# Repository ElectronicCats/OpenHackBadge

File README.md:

# Badge OpenHack Guatemala

Este es un badge electronico que hemos creado para nuestros amigos de OpenHack Guatemala 2019, en este repositorio encontraras todos los archivos necesarios para conocer el badge, ahora saca el maximo pontencial de tu badge.

### Installation Instructions

**Install SAMD soport**

You must install the boards SAMD of Arduino(vertions 1.6.11 o posterior) 

In the menú bar selec tools --> boards --> Board Manager --> Arduino SAMD Boards 32 bit M0.

In the search bar write  "SAMD" en then you can see the boards, do clic in install and wait to finish to installe.

To add board support for our products, start Arduino and open the Preferences window (**File** > **Preferences**). Now copy and paste the following URL into the 'Additional Boards Manager URLs' input field:

	https://electroniccats.github.io/Arduino_Boards_Index/package_electroniccats_index.json

- If there is already an URL from another manufacturer in that field, click the button at the right end of the field. This will open an editing window allowing you to paste the above URL onto a new line.

- Press the "OK" button.
- Open the "boards manager" that is in tools --> Board --> board manager.
- Now write "Electronic Cats" (without quotes) in the search bar.
- Click in install, jus wait to finish to install and only close the window. 

- In tools --> Boards, scroll to down in the board´s list you can see the Electronic Cat´s boards.

8. Close Boards Manager, then click Tools->Board->samd11 generic.
9. Select the MCU with the now visible Tools->Microcontroller menu (if present).
10. If you do not already have the bootloader or blink sketch installed, see SAM-BA USB CDC Bootloader below.
11. Plug in the board. The blink sketch should be running.
12. Click Tools->Port and choose the COM port. Note that the board indicated may not match the chosen board*
13. You can now upload your own sketch.

*Currently, with Electronic Cats boards, USB PIDs are shared across boards (but they are different based on Tools->USB Config).*
*This will result in Tools->Port showing "MattairTech Xeno Mini", for example, for all MattairTech boards.*

### Uploading the First Sketch

1. In the Arduino IDE (1.6.7 or above), open File->OpenFiles->Fw->Blink.
2. Be sure the correct options are selected in the Tools menu (see Core Installation above).
3. With the board plugged in, select the correct port from Tools->Port.
4. Click the Upload button. After compiling, the sketch should be transferred to the board.
5. Once the bootloader exits, the blink sketch should be running.

## License

Designed by Electronic Cats.

Firmware released under an GNU AGPL v3.0 license. See the LICENSE file for more information.

Hardware released under an CERN Open Hardware Licence v1.2. See the LICENSE_HARDWARE file for more information.

Electronic Cats is a registered trademark, please do not use if you sell these PCBs.
 
OpenHack is a registered trademark, please do not use if you sell these PCBs.

22 Oct 2019

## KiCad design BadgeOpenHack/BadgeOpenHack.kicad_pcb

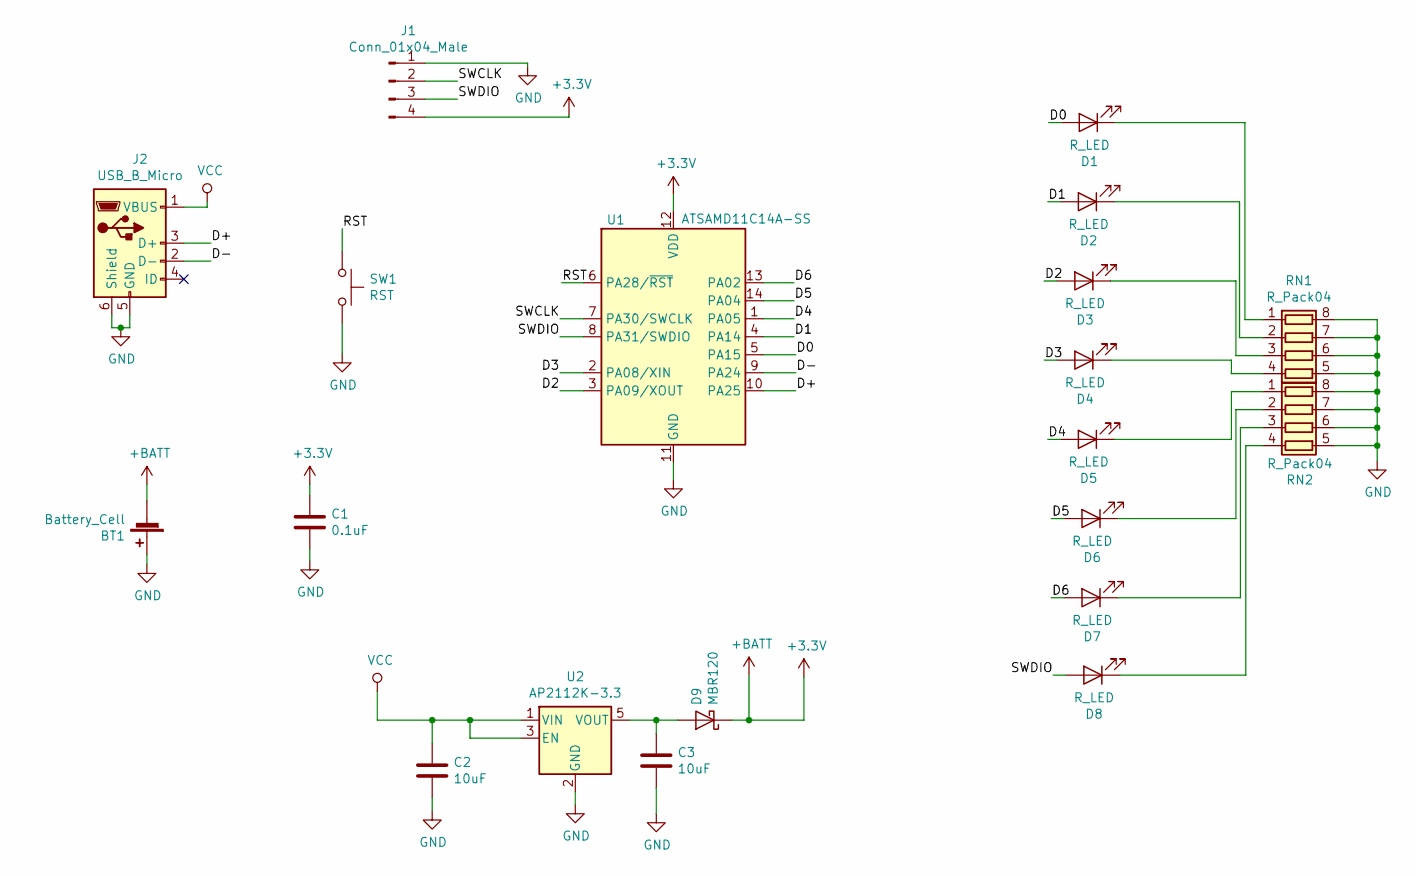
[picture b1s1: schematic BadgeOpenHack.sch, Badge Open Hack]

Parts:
BT1: Battery_Cell; BAT-HLD-012-SMT-OTL
C1: 0.1uF; C_0805_2012Metric_Pad1.15x1.40mm_HandSolder
C2, C3: 10uF; C_0805_2012Metric_Pad1.15x1.40mm_HandSolder
D1, D2, D3, D4, D5, D6, D7, D8: R_LED; LYT77K-K2M1-NoHole
D9: MBR120; D_SOD-123F
J1: Conn_01x04_Male; PinSocket_1x04_P2.54mm_Vertical
J2: USB_B_Micro; USB_Micro-B_Wuerth_629105150521
RN1, RN2: R_Pack04; R_Array_Convex_4x0603
SW1: RST; SW_SPST_TL3342
U1: ATSAMD11C14A-SS; SOIC-14_3.9x8.7mm_P1.27mm
U2: AP2112K-3.3; SOT-23-5

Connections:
+3V3: BT1.2 (-), C1.1, D9.1 (K), J1.4, U1.12 (VDD)
/D0: D1.2 (A), U1.5 (PA15)
/D1: D2.2 (A), U1.4 (PA14)
/D2: D3.2 (A), U1.3 (PA09/XOUT)
/D3: D4.2 (A), U1.2 (PA08/XIN)
/D4: D5.2 (A), U1.1 (PA05)
/D5: D6.2 (A), U1.14 (PA04)
/D6: D7.2 (A), U1.13 (PA02)
/D+: J2.3 (D+), U1.10 (PA25)
/D-: J2.2 (D-), U1.9 (PA24)
/RST: SW1.1, U1.6 (PA28/~RST)
/SWCLK: J1.2, U1.7 (PA30/SWCLK)
/SWDIO: D8.2 (A), J1.3, U1.8 (PA31/SWDIO)
GND: BT1.1 (+), C1.2, C2.2, C3.2, J1.1, J2.5 (GND), J2.6 (Shield), RN1.5 (R4.2), RN1.6 (R3.2), RN1.7 (R2.2), RN1.8 (R1.2), RN2.5 (R4.2), RN2.6 (R3.2), RN2.7 (R2.2), RN2.8 (R1.2), SW1.2, U1.11 (GND), U2.2 (GND)
unnamed: C3.1, D9.2 (A), U2.5 (VOUT)
unnamed: D1.1 (K), RN1.1 (R1.1)
unnamed: D2.1 (K), RN1.2 (R2.1)
unnamed: D3.1 (K), RN1.3 (R3.1)
unnamed: D4.1 (K), RN1.4 (R4.1)
unnamed: D5.1 (K), RN2.1 (R1.1)
unnamed: D6.1 (K), RN2.2 (R2.1)
unnamed: D7.1 (K), RN2.3 (R3.1)
unnamed: D8.1 (K), RN2.4 (R4.1)
VCC: C2.1, J2.1 (VBUS), U2.1 (VIN), U2.3 (EN)

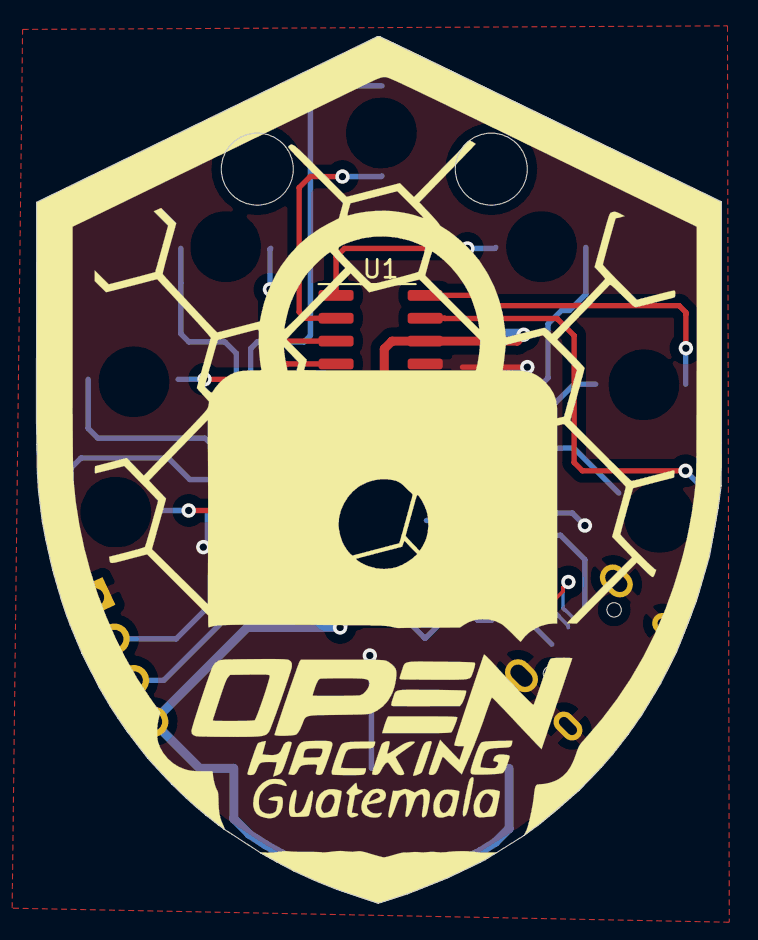
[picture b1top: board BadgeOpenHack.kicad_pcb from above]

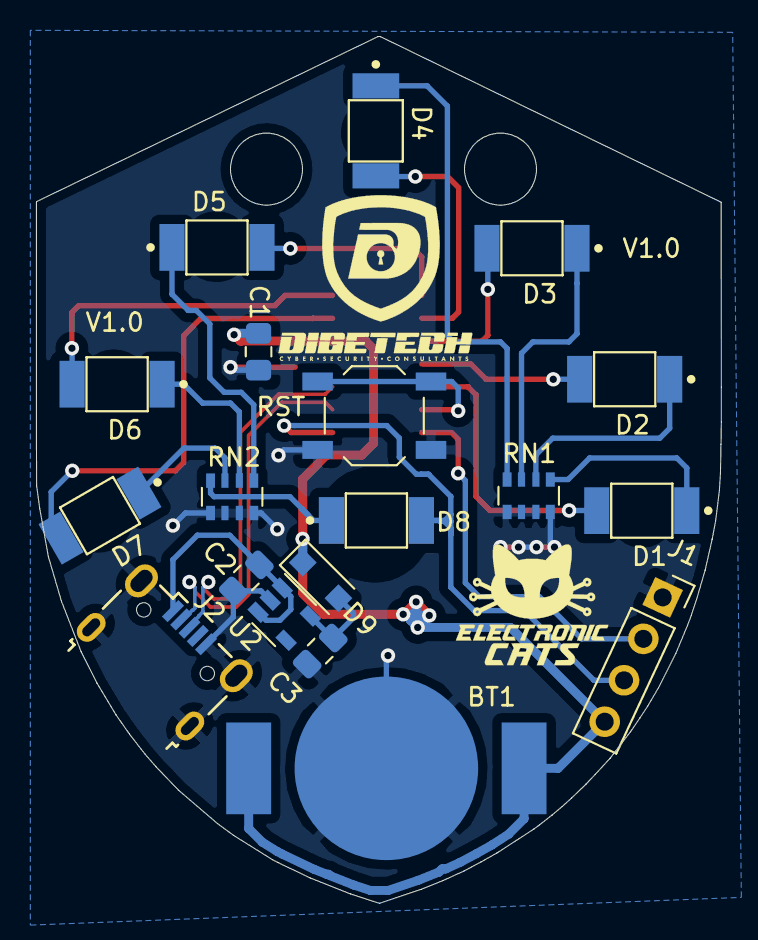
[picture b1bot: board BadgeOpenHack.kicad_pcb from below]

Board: 2 copper layers, 38.1 x 48.2 mm, 22 parts (19 on the bottom side), 24 nets.

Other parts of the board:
Ref**: Val**; seguridad-03
Ref**#2: Val**; seguridad-03

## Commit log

2019-09-03 init schematic
2019-09-04 pcb propuesta
2019-09-04 add gitignore
2019-09-04 info cache
2019-09-06 Update schematics change footprints and floorplan
    TODO:
    - Change SAMD11 to LEDs pins
    - Add reset button
    - Add action button
    - add hole for lanyard
2019-09-06 Update LED arrange almost route
2019-09-06 add rst button complete route
2019-09-06 Fix traces
2019-09-06 Add 3D renders
2019-09-06 remove logos inncesary
2019-09-06 Fix logos and vias
2019-10-29 update pcb
2019-10-29 add images
2019-10-29 add test and blink
2019-10-29 Create LICENSE_HARDWARE
2019-10-29 Create LICENSE
2019-10-29 update README with Electronic Cats core
